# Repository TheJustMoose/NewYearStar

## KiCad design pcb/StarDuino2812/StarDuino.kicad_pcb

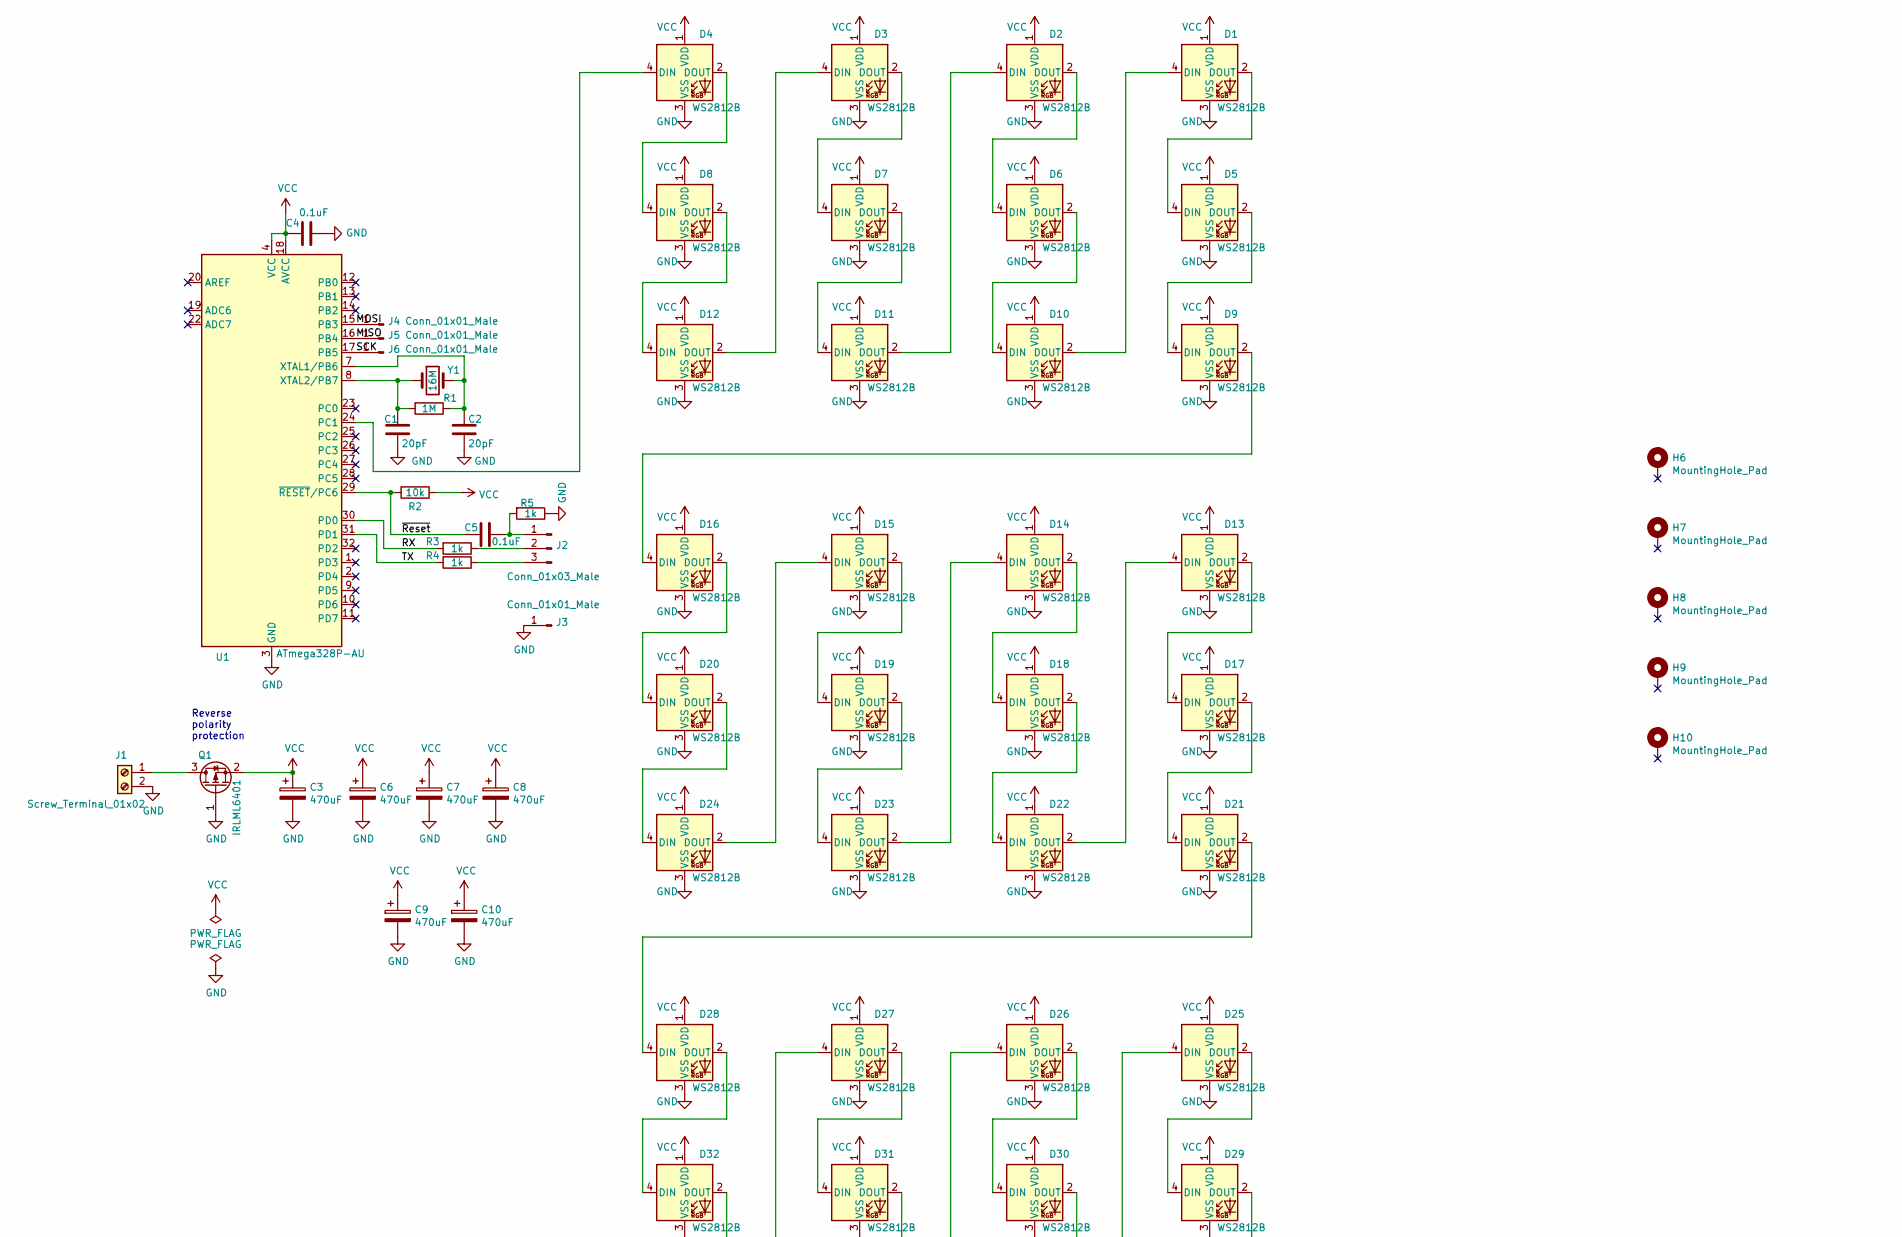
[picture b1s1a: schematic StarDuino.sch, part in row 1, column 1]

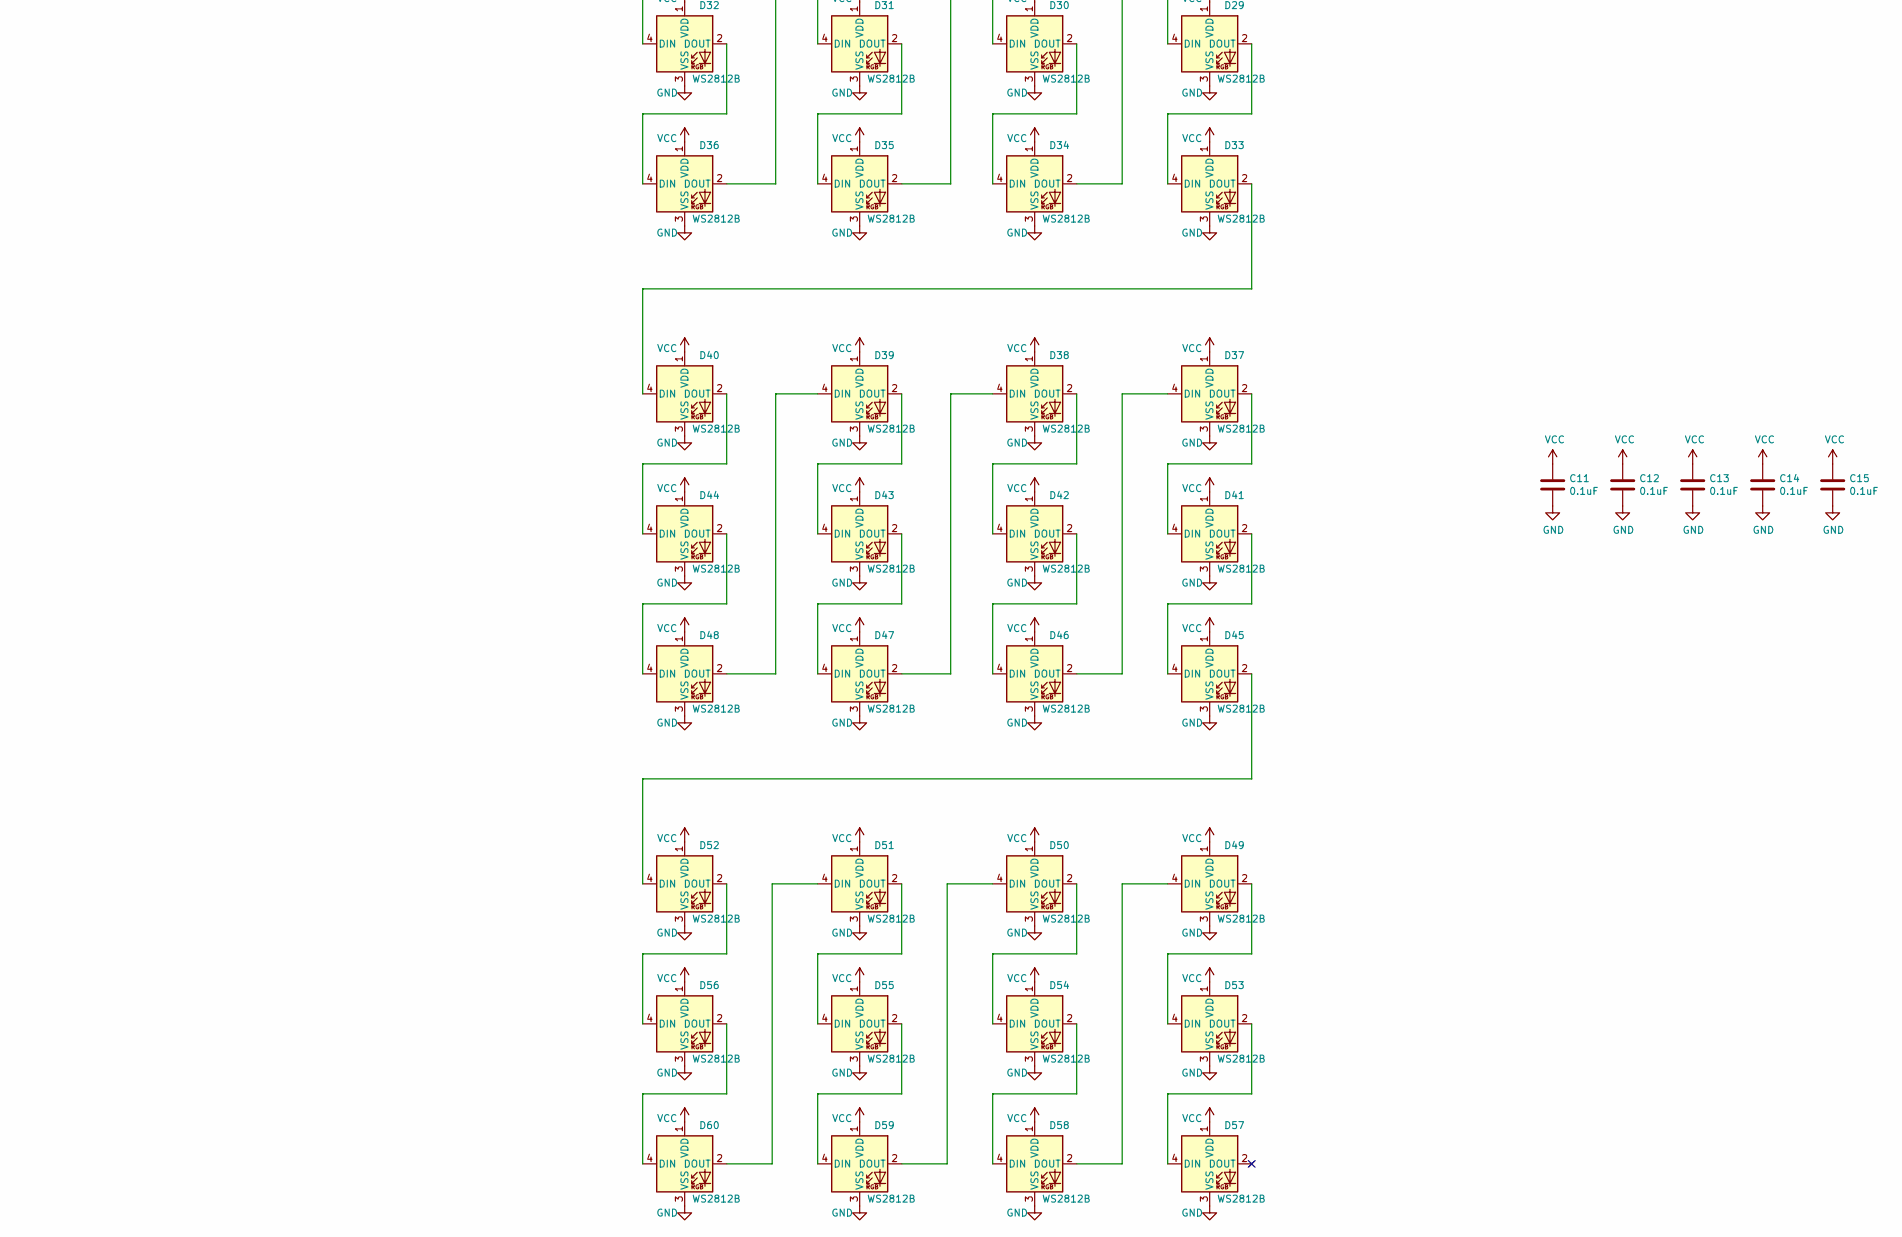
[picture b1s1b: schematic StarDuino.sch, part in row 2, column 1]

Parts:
C1, C2: 20pF; C_0805_2012Metric_Pad1.18x1.45mm_HandSolder
C3: 470uF; CP_Radial_D8.0mm_P2.50mm
C4, C5: 0.1uF; C_0805_2012Metric_Pad1.18x1.45mm_HandSolder
C6, C7, C8, C9, C10: 470uF; CP_Axial_L20.0mm_D10.0mm_P26.00mm_Horizontal
C11, C12, C13, C14, C15: 0.1uF; C-disk-15mm
D1, D2, D3, D4, D5, D6, D7, D8, D9, D10, D11, D12, D13, D14, D15, D16, D17, D18, D19, D20, D21, D22, D23, D24, D25, D26, D27, D28, D29, D30, D31, D32, D33, D34, D35, D36, D37, D38, D39, D40, D41, D42, D43, D44, D45, D46, D47, D48, D49, D50, D51, D52, D53, D54, D55, D56, D57, D58, D59, D60: WS2812B; LED_WS2812B_PLCC4_5.0x5.0mm_P3.2mm
H6, H7, H8, H9, H10: MountingHole_Pad; MountingHole_2.5mm_Pad_Via
J1: Screw_Terminal_01x02; TerminalBlock_Phoenix_MKDS-1,5-2_1x02_P5.00mm_Horizontal
J2: Conn_01x03_Male; PinHeader_1x03_P2.54mm_Vertical
J3, J4, J5, J6: Conn_01x01_Male; PinHeader_1x01_P2.54mm_Vertical
Q1: IRLML6401; SOT-23
R1: 1M; R_0805_2012Metric_Pad1.20x1.40mm_HandSolder
R2: 10k; R_0805_2012Metric_Pad1.20x1.40mm_HandSolder
R3, R4, R5: 1k; R_0805_2012Metric_Pad1.20x1.40mm_HandSolder
U1: ATmega328P-AU; TQFP-32_7x7mm_P0.8mm
Y1: 16M; Crystal_HC49-4H_Vertical

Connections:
/MISO: J5.1, U1.16 (PB4)
/MOSI: J4.1, U1.15 (PB3)
/RX: R3.2, U1.30 (PD0)
/SCK: J6.1, U1.17 (PB5)
/TX: R4.2, U1.31 (PD1)
/~Reset: C5.2, R2.2, U1.29 (~RESET~/PC6)
GND: C1.2, C2.2, C3.2, C4.1, C6.2, C7.2, C8.2, C9.2, C10.2, C11.2, C12.2, C13.2, C14.2, C15.2, D1.3 (VSS), D2.3 (VSS), D3.3 (VSS), D4.3 (VSS), D5.3 (VSS), D6.3 (VSS), D7.3 (VSS), D8.3 (VSS), D9.3 (VSS), D10.3 (VSS), D11.3 (VSS), D12.3 (VSS), D13.3 (VSS), D14.3 (VSS), D15.3 (VSS), D16.3 (VSS), D17.3 (VSS), D18.3 (VSS), D19.3 (VSS), D20.3 (VSS), D21.3 (VSS), D22.3 (VSS), D23.3 (VSS), D24.3 (VSS), D25.3 (VSS), D26.3 (VSS), D27.3 (VSS), D28.3 (VSS), D29.3 (VSS), D30.3 (VSS), D31.3 (VSS), D32.3 (VSS), D33.3 (VSS), D34.3 (VSS), D35.3 (VSS), D36.3 (VSS), D37.3 (VSS), D38.3 (VSS), D39.3 (VSS), D40.3 (VSS), D41.3 (VSS), D42.3 (VSS), D43.3 (VSS), D44.3 (VSS), D45.3 (VSS), D46.3 (VSS), D47.3 (VSS), D48.3 (VSS), D49.3 (VSS), D50.3 (VSS), D51.3 (VSS), D52.3 (VSS), D53.3 (VSS), D54.3 (VSS), D55.3 (VSS), D56.3 (VSS), D57.3 (VSS), D58.3 (VSS), D59.3 (VSS), D60.3 (VSS), J1.2, J3.1, Q1.1 (G), R5.1, U1.3 (GND), U1.5 (GND), U1.21 (GND)
unnamed: C1.1, R1.2, U1.8 (XTAL2/PB7), Y1.1
unnamed: C2.1, R1.1, U1.7 (XTAL1/PB6), Y1.2
unnamed: C5.1, J2.1, R5.2
unnamed: D1.2 (DOUT), D5.4 (DIN)
unnamed: D1.4 (DIN), D10.2 (DOUT)
unnamed: D2.2 (DOUT), D6.4 (DIN)
unnamed: D3.2 (DOUT), D7.4 (DIN)
unnamed: D4.2 (DOUT), D8.4 (DIN)
unnamed: D4.4 (DIN), U1.24 (PC1)
unnamed: D5.2 (DOUT), D9.4 (DIN)
unnamed: D6.2 (DOUT), D10.4 (DIN)
unnamed: D2.4 (DIN), D11.2 (DOUT)
unnamed: D7.2 (DOUT), D11.4 (DIN)
unnamed: D3.4 (DIN), D12.2 (DOUT)
unnamed: D8.2 (DOUT), D12.4 (DIN)
unnamed: D13.2 (DOUT), D17.4 (DIN)
unnamed: D13.4 (DIN), D22.2 (DOUT)
unnamed: D14.2 (DOUT), D18.4 (DIN)
unnamed: D14.4 (DIN), D23.2 (DOUT)
unnamed: D15.2 (DOUT), D19.4 (DIN)
unnamed: D15.4 (DIN), D24.2 (DOUT)
unnamed: D16.2 (DOUT), D20.4 (DIN)
unnamed: D9.2 (DOUT), D16.4 (DIN)
unnamed: D17.2 (DOUT), D21.4 (DIN)
unnamed: D18.2 (DOUT), D22.4 (DIN)
unnamed: D19.2 (DOUT), D23.4 (DIN)
unnamed: D20.2 (DOUT), D24.4 (DIN)
unnamed: D21.2 (DOUT), D28.4 (DIN)
unnamed: D25.2 (DOUT), D29.4 (DIN)
unnamed: D25.4 (DIN), D34.2 (DOUT)
unnamed: D26.2 (DOUT), D30.4 (DIN)
unnamed: D26.4 (DIN), D35.2 (DOUT)
unnamed: D27.2 (DOUT), D31.4 (DIN)
unnamed: D27.4 (DIN), D36.2 (DOUT)
unnamed: D28.2 (DOUT), D32.4 (DIN)
unnamed: D29.2 (DOUT), D33.4 (DIN)
unnamed: D30.2 (DOUT), D34.4 (DIN)
unnamed: D31.2 (DOUT), D35.4 (DIN)
unnamed: D32.2 (DOUT), D36.4 (DIN)
unnamed: D33.2 (DOUT), D40.4 (DIN)
unnamed: D37.2 (DOUT), D41.4 (DIN)
unnamed: D37.4 (DIN), D46.2 (DOUT)
unnamed: D38.2 (DOUT), D42.4 (DIN)
unnamed: D38.4 (DIN), D47.2 (DOUT)
unnamed: D39.2 (DOUT), D43.4 (DIN)
unnamed: D39.4 (DIN), D48.2 (DOUT)
unnamed: D40.2 (DOUT), D44.4 (DIN)
unnamed: D41.2 (DOUT), D45.4 (DIN)
unnamed: D42.2 (DOUT), D46.4 (DIN)
unnamed: D43.2 (DOUT), D47.4 (DIN)
unnamed: D44.2 (DOUT), D48.4 (DIN)
unnamed: D45.2 (DOUT), D52.4 (DIN)
unnamed: D49.2 (DOUT), D53.4 (DIN)
unnamed: D49.4 (DIN), D58.2 (DOUT)
unnamed: D50.2 (DOUT), D54.4 (DIN)
unnamed: D50.4 (DIN), D59.2 (DOUT)
unnamed: D51.2 (DOUT), D55.4 (DIN)
unnamed: D51.4 (DIN), D60.2 (DOUT)
unnamed: D52.2 (DOUT), D56.4 (DIN)
unnamed: D53.2 (DOUT), D57.4 (DIN)
unnamed: D54.2 (DOUT), D58.4 (DIN)
unnamed: D55.2 (DOUT), D59.4 (DIN)
unnamed: D56.2 (DOUT), D60.4 (DIN)
unnamed: J1.1, Q1.3 (D)
unnamed: J2.2, R3.1
unnamed: J2.3, R4.1
VCC: C3.1, C4.2, C6.1, C7.1, C8.1, C9.1, C10.1, C11.1, C12.1, C13.1, C14.1, C15.1, D1.1 (VDD), D2.1 (VDD), D3.1 (VDD), D4.1 (VDD), D5.1 (VDD), D6.1 (VDD), D7.1 (VDD), D8.1 (VDD), D9.1 (VDD), D10.1 (VDD), D11.1 (VDD), D12.1 (VDD), D13.1 (VDD), D14.1 (VDD), D15.1 (VDD), D16.1 (VDD), D17.1 (VDD), D18.1 (VDD), D19.1 (VDD), D20.1 (VDD), D21.1 (VDD), D22.1 (VDD), D23.1 (VDD), D24.1 (VDD), D25.1 (VDD), D26.1 (VDD), D27.1 (VDD), D28.1 (VDD), D29.1 (VDD), D30.1 (VDD), D31.1 (VDD), D32.1 (VDD), D33.1 (VDD), D34.1 (VDD), D35.1 (VDD), D36.1 (VDD), D37.1 (VDD), D38.1 (VDD), D39.1 (VDD), D40.1 (VDD), D41.1 (VDD), D42.1 (VDD), D43.1 (VDD), D44.1 (VDD), D45.1 (VDD), D46.1 (VDD), D47.1 (VDD), D48.1 (VDD), D49.1 (VDD), D50.1 (VDD), D51.1 (VDD), D52.1 (VDD), D53.1 (VDD), D54.1 (VDD), D55.1 (VDD), D56.1 (VDD), D57.1 (VDD), D58.1 (VDD), D59.1 (VDD), D60.1 (VDD), Q1.2 (S), R2.1, U1.4 (VCC), U1.6 (VCC), U1.18 (AVCC)

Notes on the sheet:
Reverse polarity protection

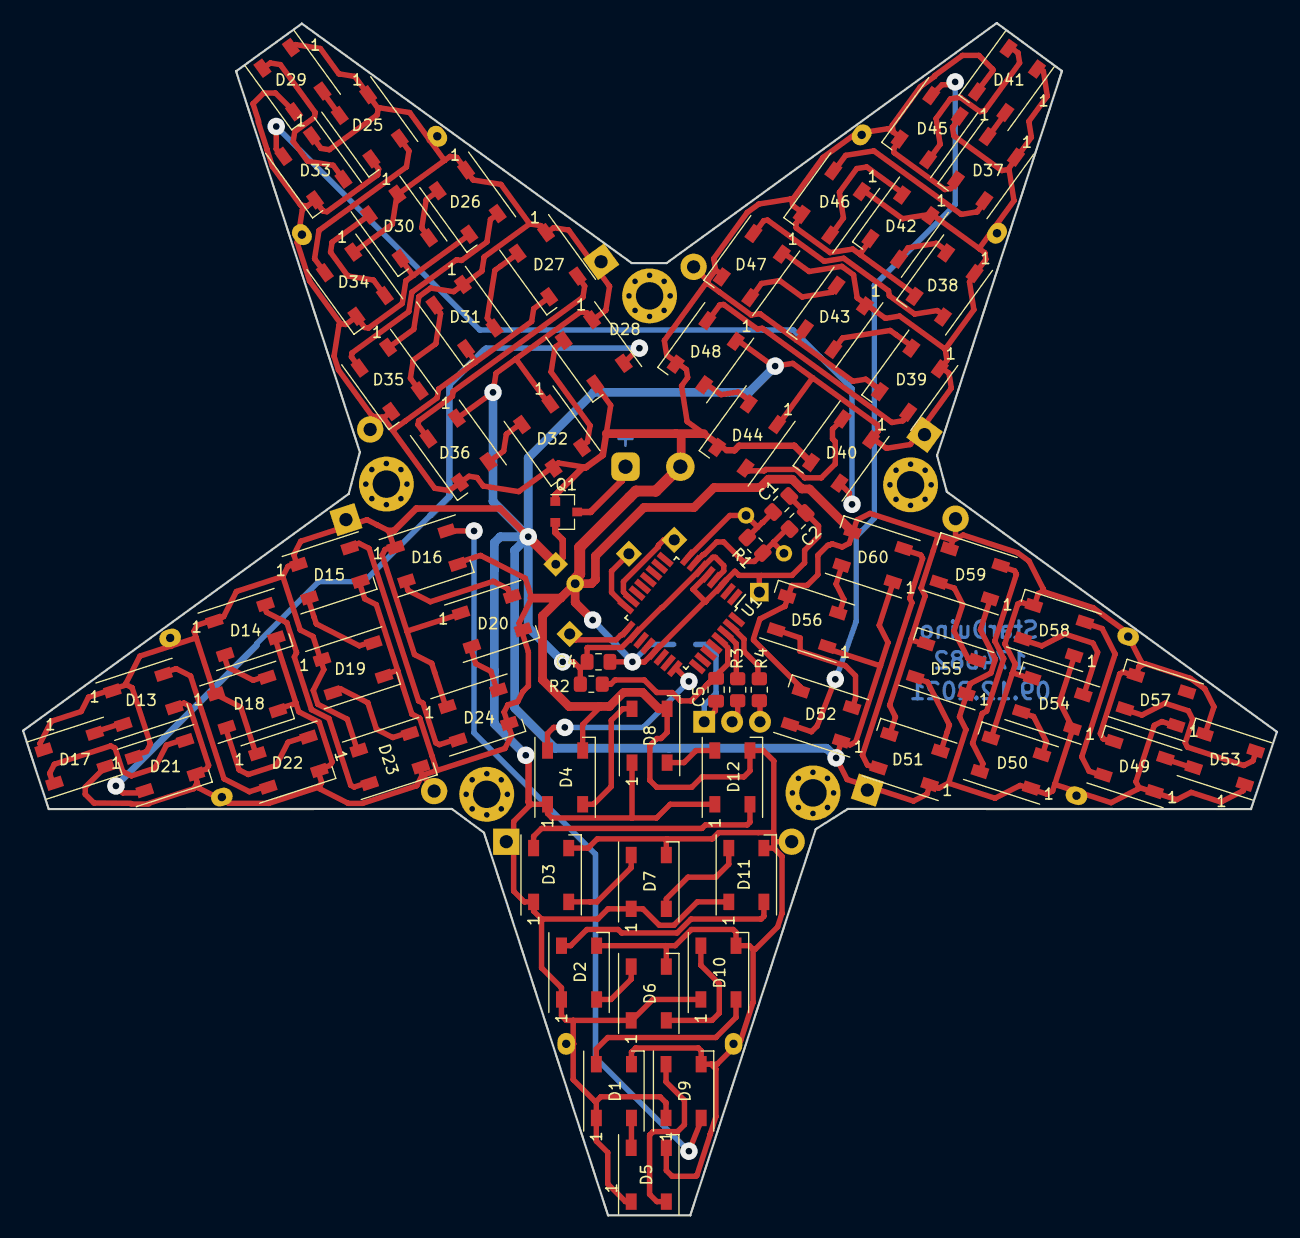
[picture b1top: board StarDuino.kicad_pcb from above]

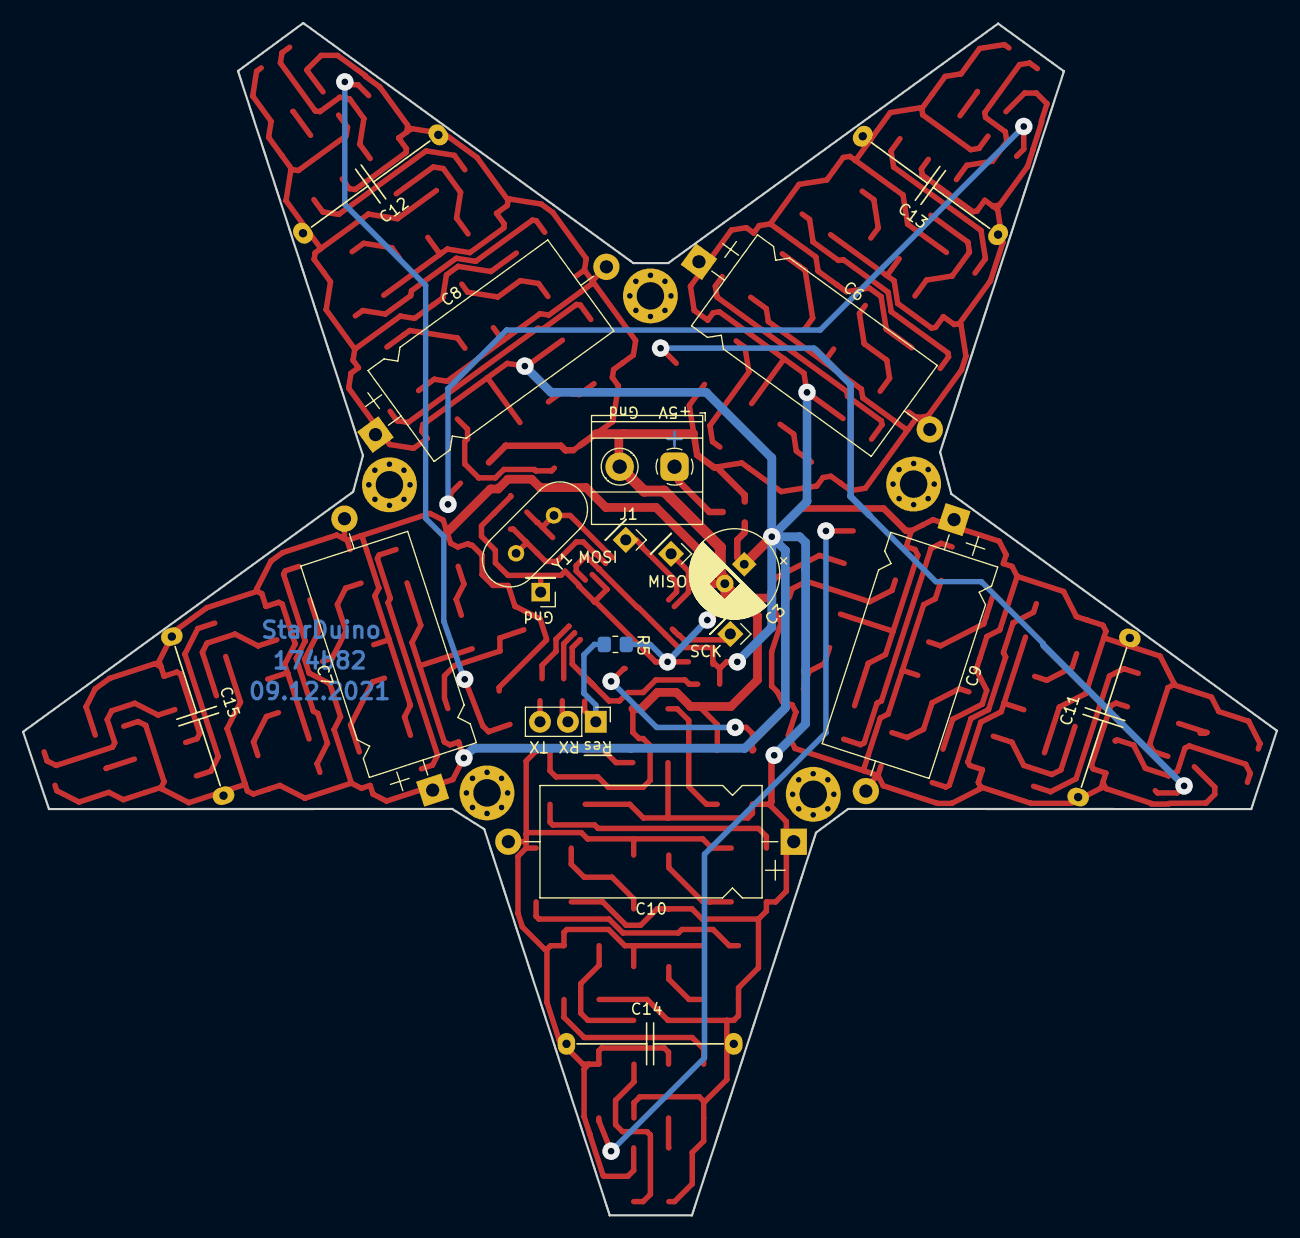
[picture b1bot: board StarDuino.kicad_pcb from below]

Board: 2 copper layers, 114.2 x 108.6 mm, 94 parts (19 on the bottom side), 74 nets.

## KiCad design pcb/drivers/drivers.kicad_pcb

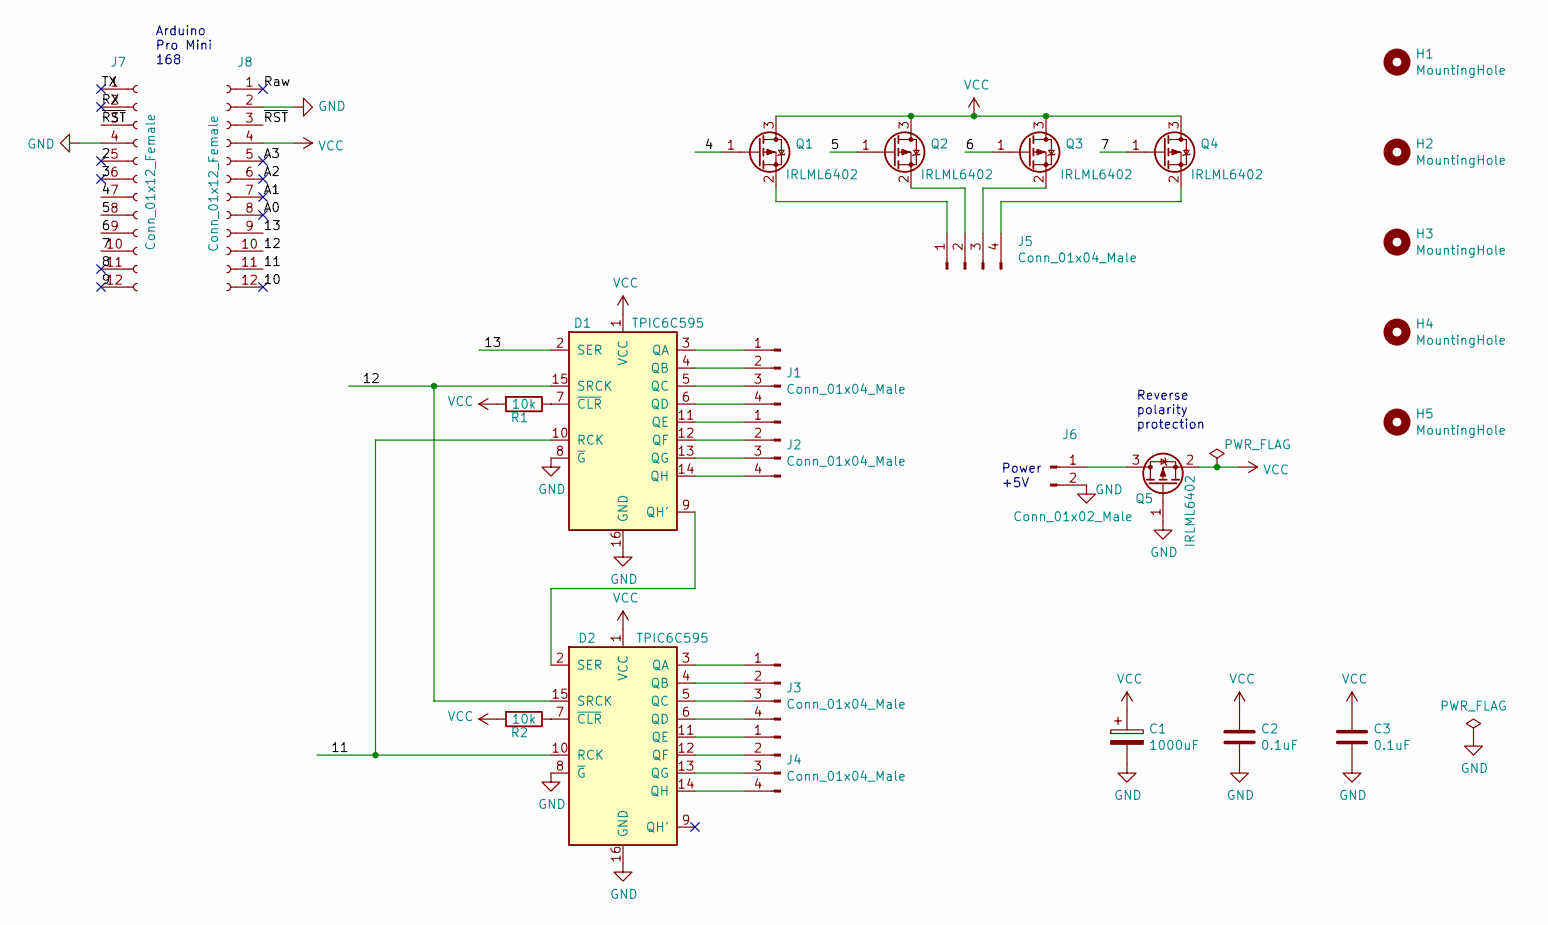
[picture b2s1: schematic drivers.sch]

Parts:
C1: 1000uF; CP_Radial_D8.0mm_P2.50mm
C2, C3: 0.1uF; C_0805_2012Metric_Pad1.18x1.45mm_HandSolder
D1, D2: TPIC6C595; DIP-16_W7.62mm
H1, H2, H3, H4, H5: MountingHole; MountingHole_3.2mm_M3
J1, J2, J3, J4, J5: Conn_01x04_Male; PinHeader_1x04_P2.54mm_Vertical
J6: Conn_01x02_Male; TerminalBlock_Phoenix_MKDS-1,5-2_1x02_P5.00mm_Horizontal
J7, J8: Conn_01x12_Female; PinSocket_1x12_P2.54mm_Vertical
Q1, Q2, Q3, Q4, Q5: IRLML6402; SOT-23
R1, R2: 10k; R_0805_2012Metric_Pad1.20x1.40mm_HandSolder

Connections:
/2: J7.5
/3: J7.6
/4: J7.7, Q1.1 (G)
/5: J7.8, Q2.1 (G)
/6: J7.9, Q3.1 (G)
/7: J7.10, Q4.1 (G)
/8: J7.11
/9: J7.12
/10: J8.12
/11: D1.10 (RCK), D2.10 (RCK), J8.11
/12: D1.15 (SRCK), D2.15 (SRCK), J8.10
/13: D1.2 (SER), J8.9
/A0: J8.8
/A1: J8.7
/A2: J8.6
/A3: J8.5
/RX: J7.2
/Raw: J8.1
/TX: J7.1
/~RST: J7.3, J8.3
GND: C1.2, C2.2, C3.2, D1.8 (~G), D1.16 (GND), D2.8 (~G), D2.16 (GND), J6.2, J7.4, J8.2, Q5.1 (G)
unnamed: D1.3 (QA), J1.1
unnamed: D1.4 (QB), J1.2
unnamed: D1.5 (QC), J1.3
unnamed: D1.6 (QD), J1.4
unnamed: D1.7 (~CLR), R1.1
unnamed: D1.9 (QH'), D2.2 (SER)
unnamed: D1.11 (QE), J2.1
unnamed: D1.12 (QF), J2.2
unnamed: D1.13 (QG), J2.3
unnamed: D1.14 (QH), J2.4
unnamed: D2.3 (QA), J3.1
unnamed: D2.4 (QB), J3.2
unnamed: D2.5 (QC), J3.3
unnamed: D2.6 (QD), J3.4
unnamed: D2.7 (~CLR), R2.1
unnamed: D2.11 (QE), J4.1
unnamed: D2.12 (QF), J4.2
unnamed: D2.13 (QG), J4.3
unnamed: D2.14 (QH), J4.4
unnamed: J5.1, Q1.2 (S)
unnamed: J5.2, Q2.2 (S)
unnamed: J5.3, Q3.2 (S)
unnamed: J5.4, Q4.2 (S)
unnamed: J6.1, Q5.3 (D)
VCC: C1.1, C2.1, C3.1, D1.1 (VCC), D2.1 (VCC), J8.4, Q1.3 (D), Q2.3 (D), Q3.3 (D), Q4.3 (D), Q5.2 (S), R1.2, R2.2

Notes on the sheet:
Power +5V
Reverse polarity protection
Arduino Pro Mini 168

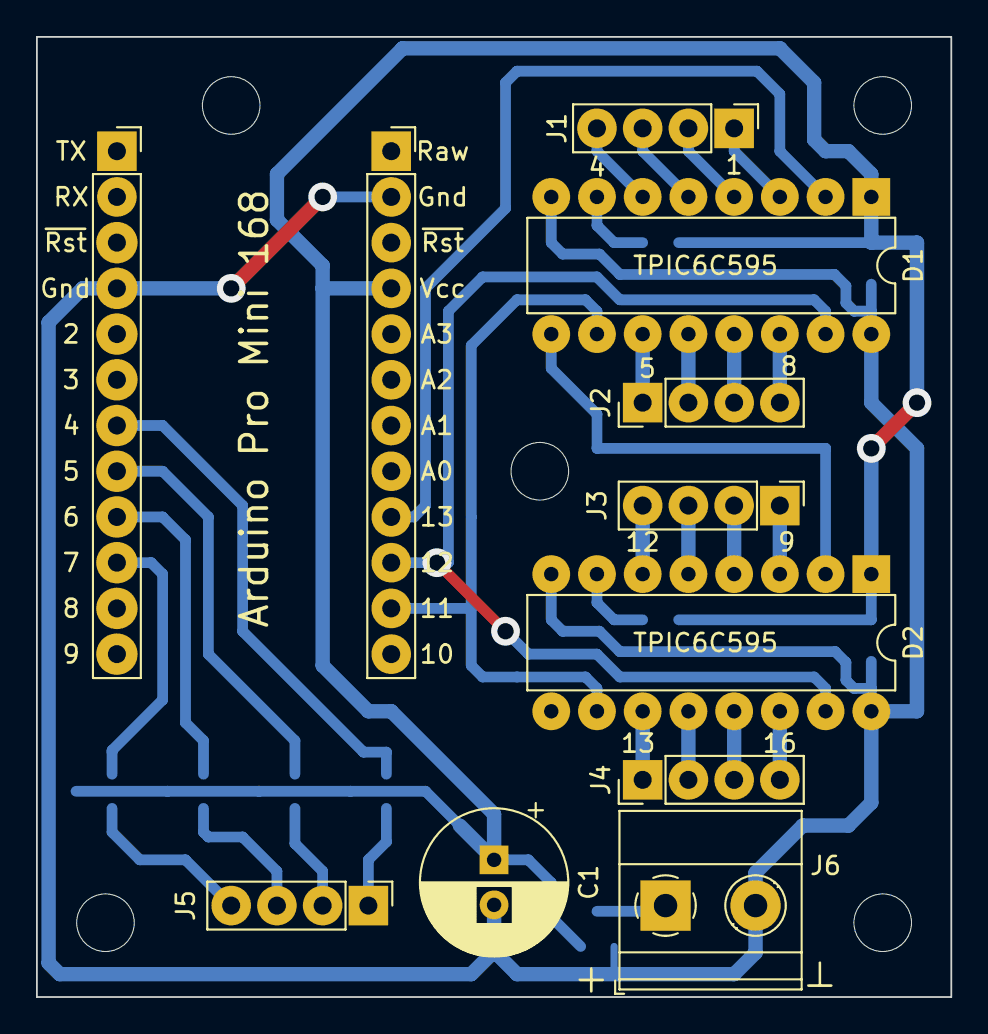
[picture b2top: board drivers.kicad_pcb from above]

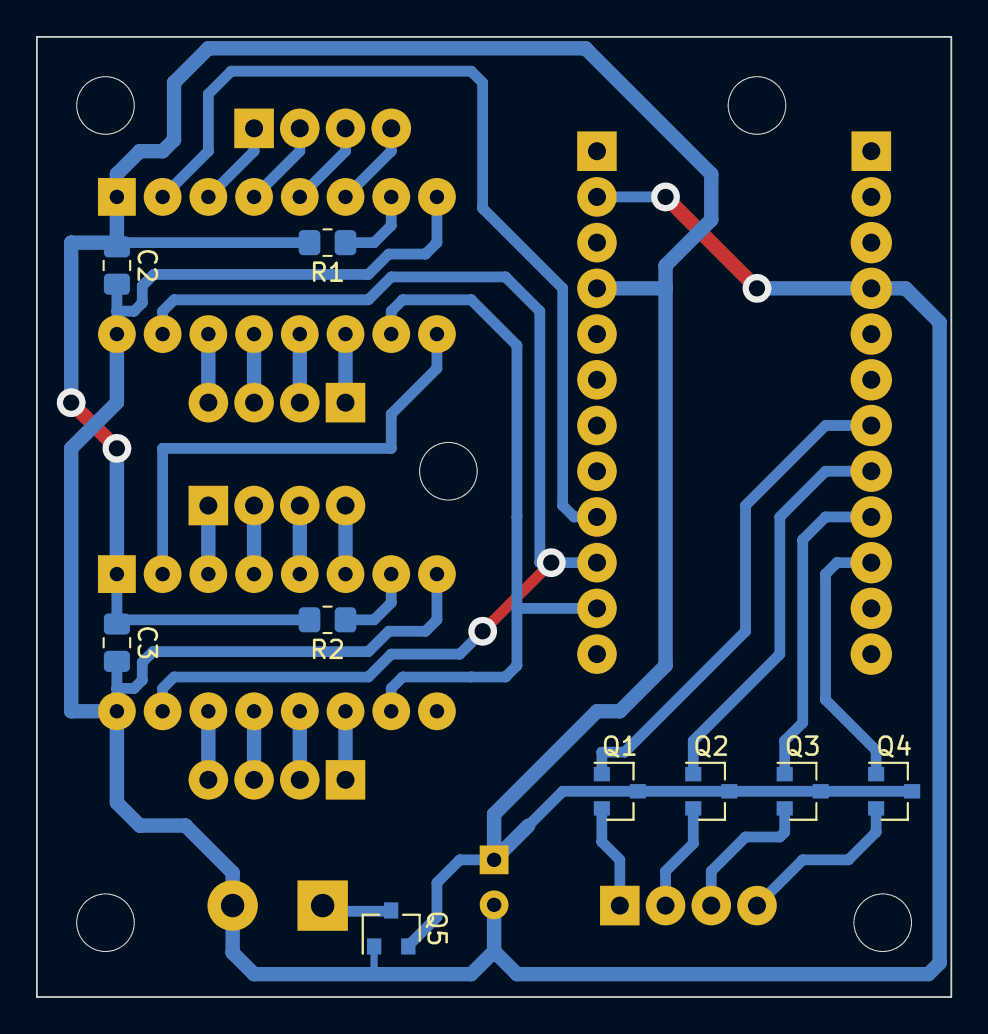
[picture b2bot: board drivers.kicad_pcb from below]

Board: 2 copper layers, 50.8 x 53.3 mm, 25 parts (9 on the bottom side), 34 nets.

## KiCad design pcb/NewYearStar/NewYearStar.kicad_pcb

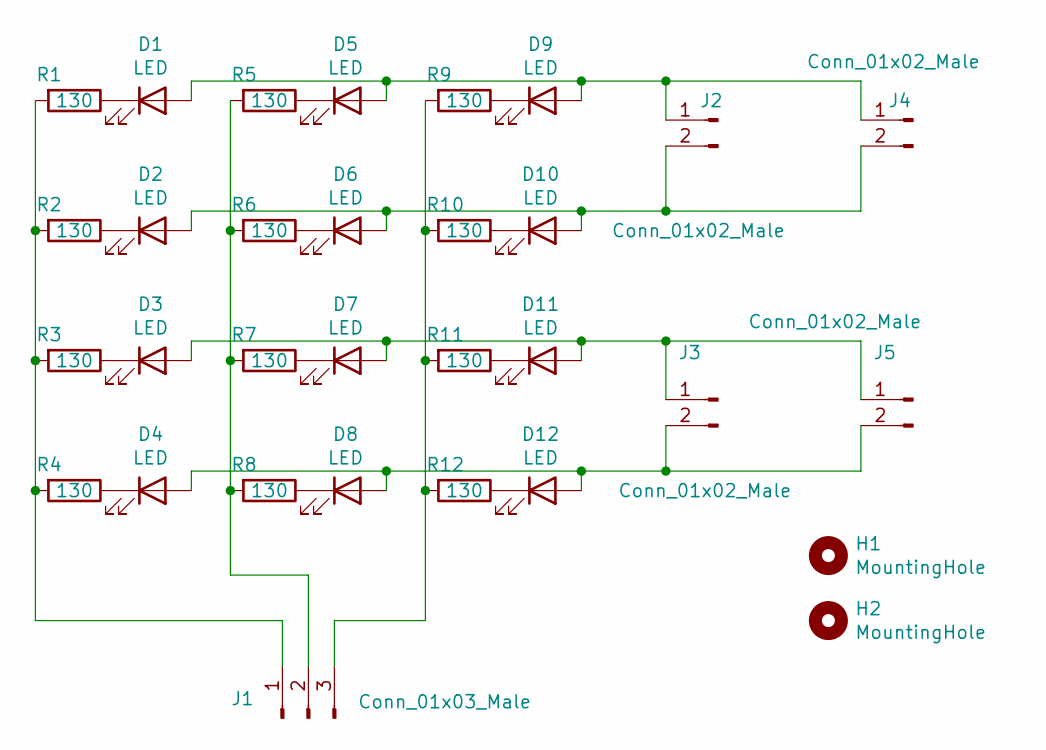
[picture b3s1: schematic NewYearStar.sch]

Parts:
D1, D2, D3, D4, D5, D6, D7, D8, D9, D10, D11, D12: LED; LED_D5.0mm
H1, H2: MountingHole; MountingHole_2.5mm
J1: Conn_01x03_Male; PinHeader_1x03_P2.54mm_Vertical
J2, J3, J4, J5: Conn_01x02_Male; PinHeader_1x02_P2.54mm_Vertical
R1, R2, R3, R4, R5, R6, R7, R8, R9, R10, R11, R12: 130; R_0805_2012Metric_Pad1.20x1.40mm_HandSolder

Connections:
unnamed: D1.1 (K), R1.1
unnamed: D1.2 (A), D5.2 (A), D9.2 (A), J2.1, J4.1
unnamed: D2.1 (K), R2.1
unnamed: D3.1 (K), R3.1
unnamed: D4.1 (K), R4.1
unnamed: D5.1 (K), R5.1
unnamed: D6.1 (K), R6.1
unnamed: D7.1 (K), R7.1
unnamed: D8.1 (K), R8.1
unnamed: D9.1 (K), R9.1
unnamed: D10.1 (K), R10.1
unnamed: D2.2 (A), D6.2 (A), D10.2 (A), J2.2, J4.2
unnamed: D11.1 (K), R11.1
unnamed: D3.2 (A), D7.2 (A), D11.2 (A), J3.1, J5.1
unnamed: D12.1 (K), R12.1
unnamed: D4.2 (A), D8.2 (A), D12.2 (A), J3.2, J5.2
unnamed: J1.1, R1.2, R2.2, R3.2, R4.2
unnamed: J1.2, R5.2, R6.2, R7.2, R8.2
unnamed: J1.3, R9.2, R10.2, R11.2, R12.2

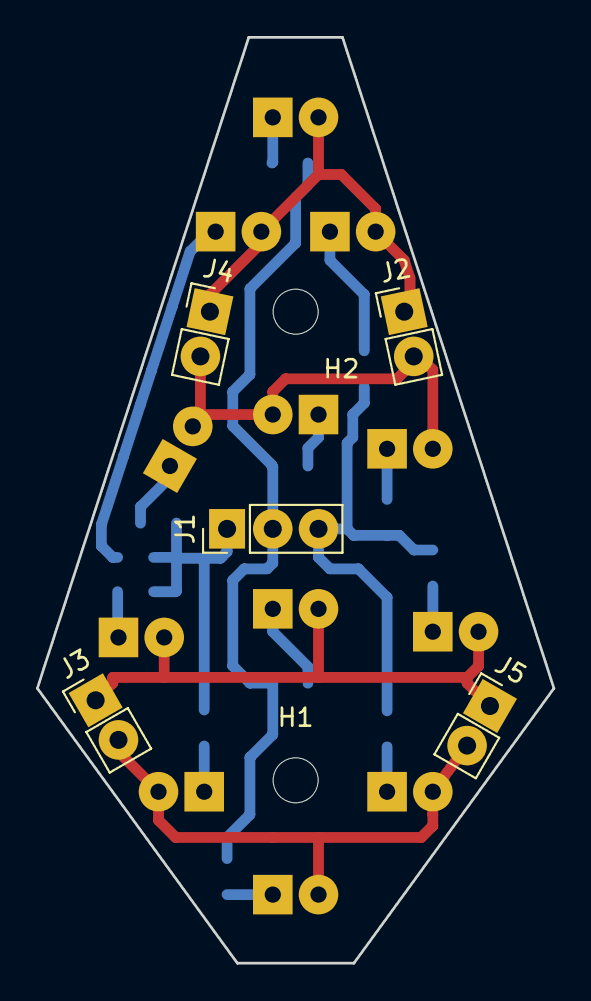
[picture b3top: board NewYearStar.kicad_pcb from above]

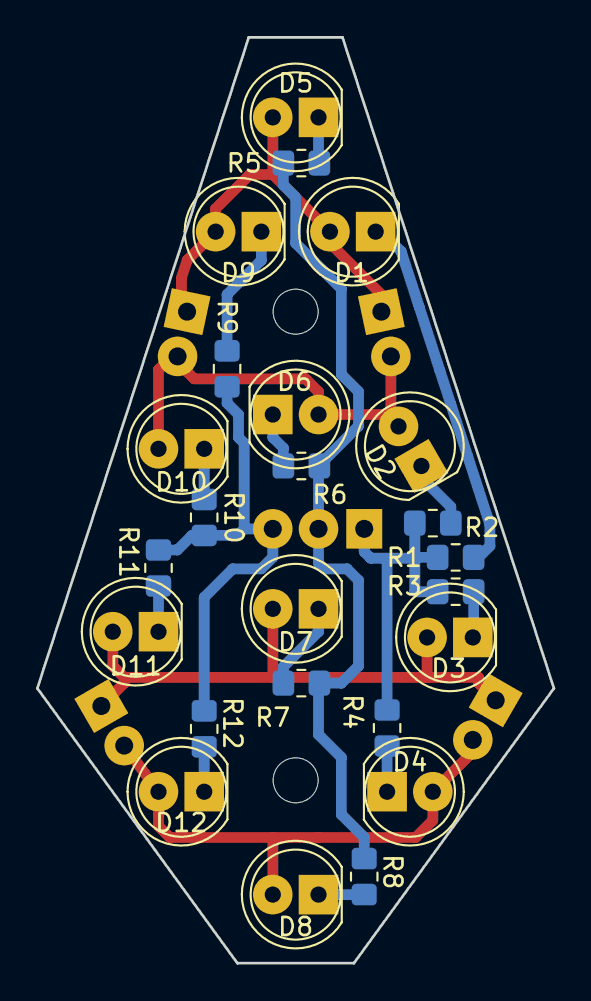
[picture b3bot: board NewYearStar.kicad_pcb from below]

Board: 2 copper layers, 28.7 x 51.4 mm, 31 parts (24 on the bottom side), 19 nets.

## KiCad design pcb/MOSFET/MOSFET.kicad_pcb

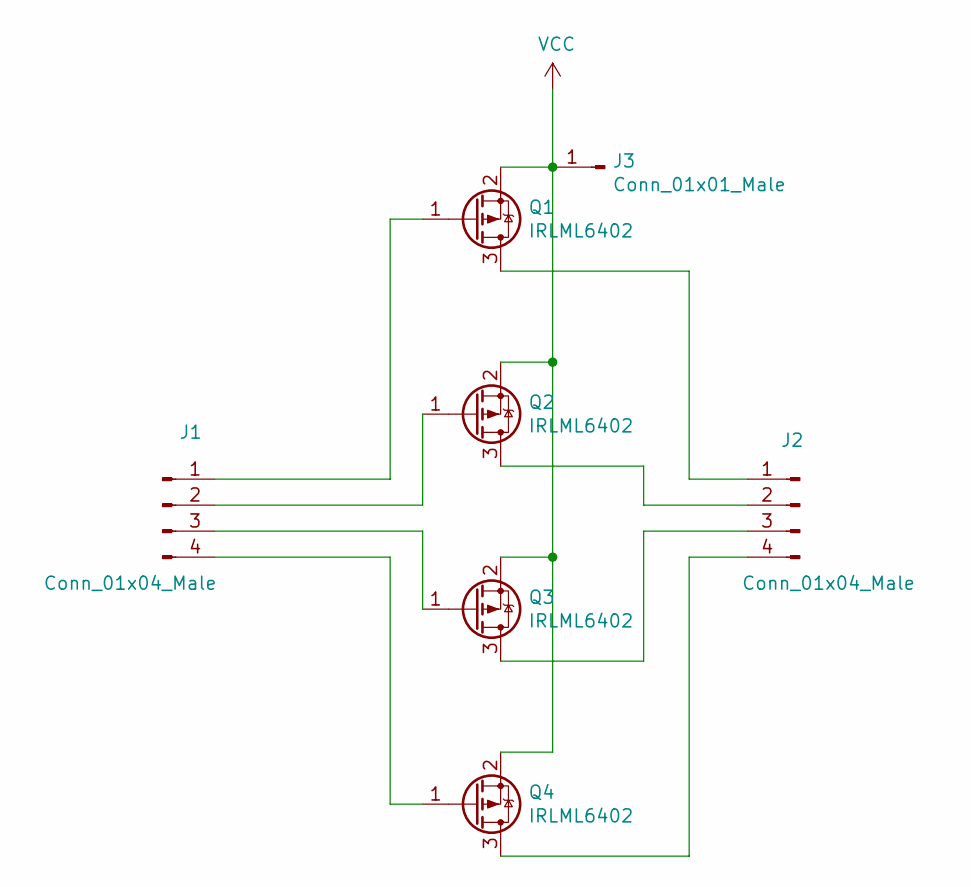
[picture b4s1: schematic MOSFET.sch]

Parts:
J1, J2: Conn_01x04_Male; PinHeader_1x04_P2.54mm_Vertical
J3: Conn_01x01_Male; PinHeader_1x01_P2.54mm_Vertical
Q1, Q2, Q3, Q4: IRLML6402; SOT-23

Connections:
unnamed: J1.1, Q1.1 (G)
unnamed: J1.2, Q2.1 (G)
unnamed: J1.3, Q3.1 (G)
unnamed: J1.4, Q4.1 (G)
unnamed: J2.1, Q1.3 (D)
unnamed: J2.2, Q2.3 (D)
unnamed: J2.3, Q3.3 (D)
unnamed: J2.4, Q4.3 (D)
VCC: J3.1, Q1.2 (S), Q2.2 (S), Q3.2 (S), Q4.2 (S)

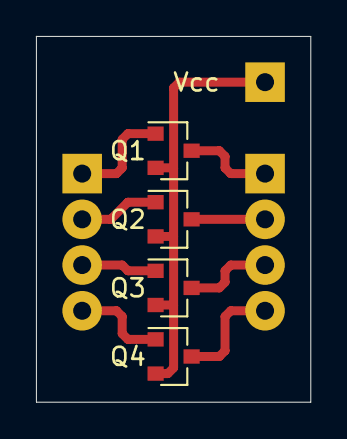
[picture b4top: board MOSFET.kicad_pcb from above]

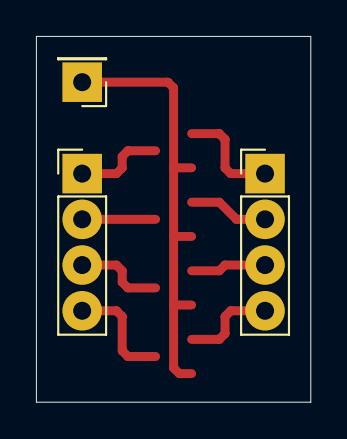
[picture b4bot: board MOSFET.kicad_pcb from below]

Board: 2 copper layers, 15.2 x 20.3 mm, 7 parts (3 on the bottom side), 9 nets.

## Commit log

2020-12-21 Add .gitignore
2020-12-21 NewYearStar pcb
2020-12-21 The box for the pcbs
2021-01-04 Firmware
2021-01-04 MOSFET pcb
2021-01-04 Some changes
2021-01-04 Add R for every LED
2021-01-08 Fix firmware
2021-01-08 Polishing
2021-01-08 Drivers pcb
2021-01-09 Replace Arduino Pro Mini to another Arduino Pro Mini
2021-01-10 Swap pin 12 and 13
2021-01-10 Align to grid
2021-01-10 Remove unused template
2021-01-23 NewYearStar v2 == WS2812B
2021-01-24 2812 star in work
2021-01-27 Cut vertexes
2021-01-27 Almost ready
2021-02-02 Add fifth hole
2021-03-12 Fix tracks
2021-03-25 Rename and move
2021-03-25 Test firmware for WS2812B star
2021-03-25 Fix LED pads
2021-03-26 Wrong silk!!!!
2021-03-27 Some new effects
2021-03-30 Fix LEDs labels
2021-03-30 Replace Mounting holes to Mounting pads Add capacitor Add resistors to UART
2021-03-31 Polishing. Add resistor, silk, etc
2021-04-06 StarDuino2812, add photomask
2021-09-19 NewYearStar2812. Add capacitors.
2021-09-22 StarDuino2812. Fix hash. Add photomask
2021-10-27 Replace disk capacitor. Add gerber.
2021-12-08 Add ISP to StarDuino
